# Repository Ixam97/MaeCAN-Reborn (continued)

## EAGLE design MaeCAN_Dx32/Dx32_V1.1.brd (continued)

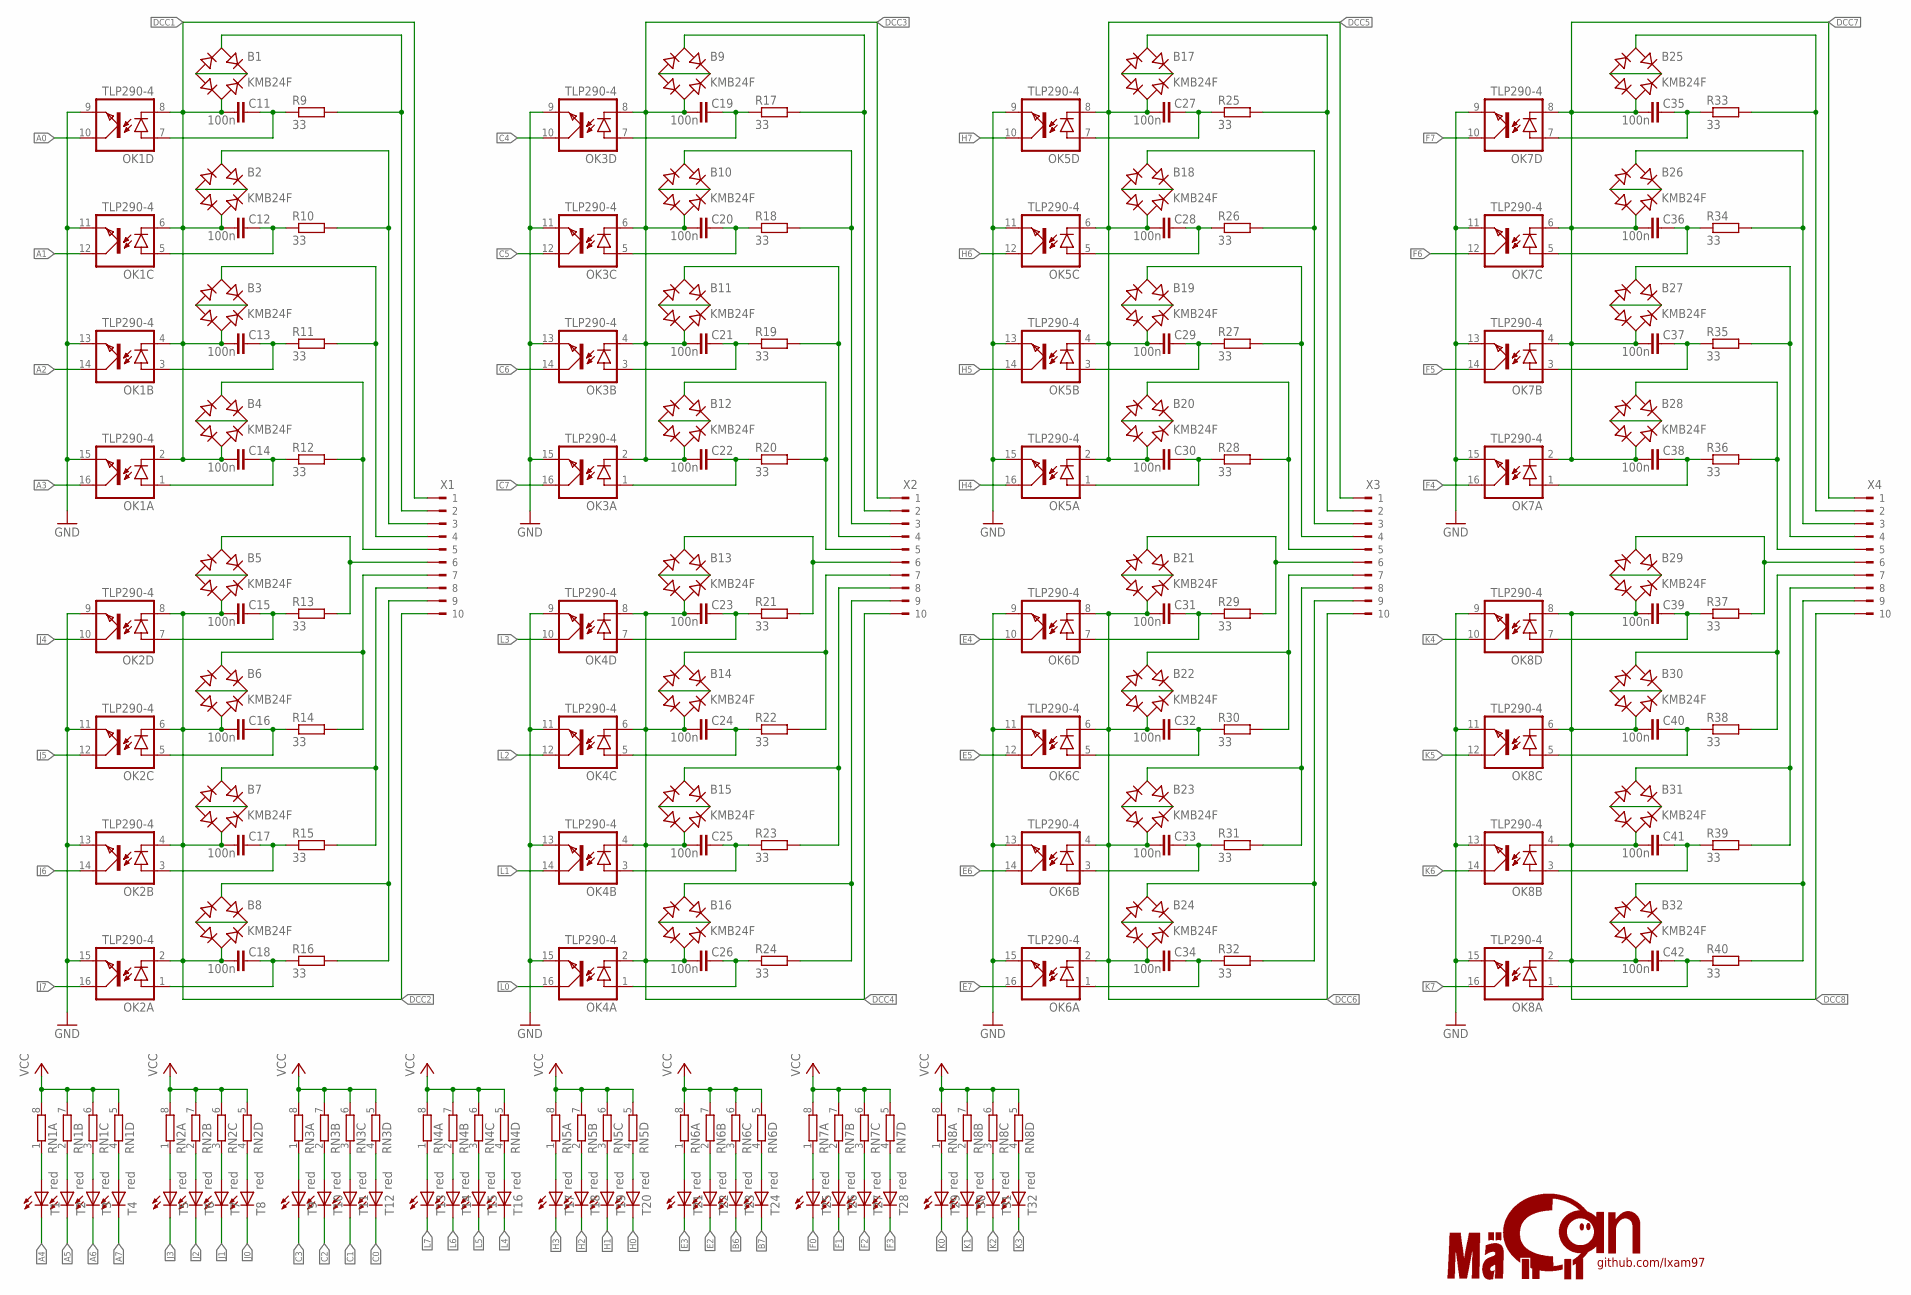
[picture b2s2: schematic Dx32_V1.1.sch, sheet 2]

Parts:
B1: KMB24F; MBS; JLCPCB-PART C113927
B2, B3, B4, B5, B6, B7, B8, B9, B10, B11, B12, B13, B14, B15, B16, B17, B18, B19, B20, B21, B22, B23, B24, B25, B26, B27, B28, B29, B30, B31, B32: KMB24F; MBS
C11, C12, C13, C14, C15, C16, C17, C18, C19, C20, C21, C22, C23, C24, C25, C26, C27, C28, C29, C30, C31, C32, C33, C34, C35, C36, C37, C38, C39, C40, C41, C42: 100n; C0402
OK1: TLP290-4; MINI-FLAT-16; JLCPC-PART C39031
OK2, OK3, OK4, OK5, OK6, OK7, OK8: TLP290-4; MINI-FLAT-16
R9, R10, R11, R12, R13, R14, R15, R16, R17, R18, R19, R20, R21, R22, R23, R24, R25, R26, R27, R28, R29, R30, R31, R32, R33, R34, R35, R36, R37, R38, R39, R40: 33; R0402
RN1, RN2, RN3, RN4, RN5, RN6, RN7, RN8: 4R-N0603-ARV; 0603-ARV
T1: red; CHIP-LED0805; JLCPCB-PART C84256
T2, T3, T4, T5, T6, T7, T8, T9, T10, T11, T12, T13, T14, T15, T16, T17, T18, T19, T20, T21, T22, T23, T24, T25, T26, T27, T28, T29, T30, T31, T32: red; CHIP-LED0805
X1, X2, X3, X4: 180-10

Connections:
A0: OK1.10 (COL); also elsewhere on the board
A1: OK1.12 (COL); also elsewhere on the board
A2: OK1.14 (COL); also elsewhere on the board
A3: OK1.16 (COL); also elsewhere on the board
A4: T1.C; also elsewhere on the board
A5: T2.C; also elsewhere on the board
A6: T3.C; also elsewhere on the board
A7: T4.C; also elsewhere on the board
B6: T23.C; also elsewhere on the board
B7: T24.C; also elsewhere on the board
C0: T12.C; also elsewhere on the board
C1: T11.C; also elsewhere on the board
C2: T10.C; also elsewhere on the board
C3: T9.C; also elsewhere on the board
C4: OK3.10 (COL); also elsewhere on the board
C5: OK3.12 (COL); also elsewhere on the board
C6: OK3.14 (COL); also elsewhere on the board
C7: OK3.16 (COL); also elsewhere on the board
DCC1: B1.AC2, B2.AC2, B3.AC2, B4.AC2, C11.2, C12.2, C13.2, C14.2, OK1.2 (C), OK1.4 (C), OK1.6 (C), OK1.8 (C), X1.1
DCC2: B5.AC2, B6.AC2, B7.AC2, B8.AC2, C15.2, C16.2, C17.2, C18.2, OK2.2 (C), OK2.4 (C), OK2.6 (C), OK2.8 (C), X1.10
DCC3: B9.AC2, B10.AC2, B11.AC2, B12.AC2, C19.2, C20.2, C21.2, C22.2, OK3.2 (C), OK3.4 (C), OK3.6 (C), OK3.8 (C), X2.1
DCC4: B13.AC2, B14.AC2, B15.AC2, B16.AC2, C23.2, C24.2, C25.2, C26.2, OK4.2 (C), OK4.4 (C), OK4.6 (C), OK4.8 (C), X2.10
DCC5: B17.AC2, B18.AC2, B19.AC2, B20.AC2, C27.2, C28.2, C29.2, C30.2, OK5.2 (C), OK5.4 (C), OK5.6 (C), OK5.8 (C), X3.1
DCC6: B21.AC2, B22.AC2, B23.AC2, B24.AC2, C31.2, C32.2, C33.2, C34.2, OK6.2 (C), OK6.4 (C), OK6.6 (C), OK6.8 (C), X3.10
DCC7: B25.AC2, B26.AC2, B27.AC2, B28.AC2, C35.2, C36.2, C37.2, C38.2, OK7.2 (C), OK7.4 (C), OK7.6 (C), OK7.8 (C), X4.1
DCC8: B29.AC2, B30.AC2, B31.AC2, B32.AC2, C39.2, C40.2, C41.2, C42.2, OK8.2 (C), OK8.4 (C), OK8.6 (C), OK8.8 (C), X4.10
E2: T22.C; also elsewhere on the board
E3: T21.C; also elsewhere on the board
E4: OK6.10 (COL); also elsewhere on the board
E5: OK6.12 (COL); also elsewhere on the board
E6: OK6.14 (COL); also elsewhere on the board
E7: OK6.16 (COL); also elsewhere on the board
F0: T25.C; also elsewhere on the board
F1: T26.C; also elsewhere on the board
F2: T27.C; also elsewhere on the board
F3: T28.C; also elsewhere on the board
F4: OK7.16 (COL); also elsewhere on the board
F5: OK7.14 (COL); also elsewhere on the board
F6: OK7.12 (COL); also elsewhere on the board
F7: OK7.10 (COL); also elsewhere on the board
GND: OK1.9 (EMIT), OK1.11 (EMIT), OK1.13 (EMIT), OK1.15 (EMIT), OK2.9 (EMIT), OK2.11 (EMIT), OK2.13 (EMIT), OK2.15 (EMIT), OK3.9 (EMIT), OK3.11 (EMIT), OK3.13 (EMIT), OK3.15 (EMIT), OK4.9 (EMIT), OK4.11 (EMIT), OK4.13 (EMIT), OK4.15 (EMIT), OK5.9 (EMIT), OK5.11 (EMIT), OK5.13 (EMIT), OK5.15 (EMIT), OK6.9 (EMIT), OK6.11 (EMIT), OK6.13 (EMIT), OK6.15 (EMIT), OK7.9 (EMIT), OK7.11 (EMIT), OK7.13 (EMIT), OK7.15 (EMIT), OK8.9 (EMIT), OK8.11 (EMIT), OK8.13 (EMIT), OK8.15 (EMIT); also elsewhere on the board
H0: T20.C; also elsewhere on the board
H1: T19.C; also elsewhere on the board
H2: T18.C; also elsewhere on the board
H3: T17.C; also elsewhere on the board
H4: OK5.16 (COL); also elsewhere on the board
H5: OK5.14 (COL); also elsewhere on the board
H6: OK5.12 (COL); also elsewhere on the board
H7: OK5.10 (COL); also elsewhere on the board
J0: T8.C; also elsewhere on the board
J1: T7.C; also elsewhere on the board
J2: T6.C; also elsewhere on the board
J3: T5.C; also elsewhere on the board
J4: OK2.10 (COL); also elsewhere on the board
J5: OK2.12 (COL); also elsewhere on the board
J6: OK2.14 (COL); also elsewhere on the board
J7: OK2.16 (COL); also elsewhere on the board
K0: T29.C; also elsewhere on the board
K1: T30.C; also elsewhere on the board
K2: T31.C; also elsewhere on the board
K3: T32.C; also elsewhere on the board
K4: OK8.10 (COL); also elsewhere on the board
K5: OK8.12 (COL); also elsewhere on the board
K6: OK8.14 (COL); also elsewhere on the board
K7: OK8.16 (COL); also elsewhere on the board
L0: OK4.16 (COL); also elsewhere on the board
L1: OK4.14 (COL); also elsewhere on the board
L2: OK4.12 (COL); also elsewhere on the board
L3: OK4.10 (COL); also elsewhere on the board
L4: T16.C; also elsewhere on the board
L5: T15.C; also elsewhere on the board
L6: T14.C; also elsewhere on the board
L7: T13.C; also elsewhere on the board
unnamed: B1.+, B1.-
unnamed: B1.AC1, R9.2, X1.2
unnamed: B5.+, B5.-
unnamed: C11.1, OK1.7 (A), R9.1
unnamed: B2.+, B2.-
unnamed: B2.AC1, R10.2, X1.3
unnamed: B3.+, B3.-
unnamed: C12.1, OK1.5 (A), R10.1
unnamed: B24.AC1, R32.2, X3.9
unnamed: C13.1, OK1.3 (A), R11.1
unnamed: B4.+, B4.-
unnamed: B4.AC1, R12.2, X1.5
unnamed: C14.1, OK1.1 (A), R12.1
unnamed: B5.AC1, R13.2, X1.6
unnamed: C15.1, OK2.7 (A), R13.1
unnamed: B6.+, B6.-
unnamed: B6.AC1, R14.2, X1.7
unnamed: C16.1, OK2.5 (A), R14.1
unnamed: B7.+, B7.-
unnamed: B7.AC1, R15.2, X1.8
unnamed: C17.1, OK2.3 (A), R15.1
unnamed: B8.+, B8.-
unnamed: B8.AC1, R16.2, X1.9
unnamed: C18.1, OK2.1 (A), R16.1
unnamed: RN1.1, T1.A
unnamed: RN1.2 (1), T2.A
unnamed: RN1.3 (1), T3.A
unnamed: RN1.4 (1), T4.A
unnamed: RN2.1, T5.A
unnamed: RN2.2 (1), T6.A
unnamed: RN2.3 (1), T7.A
unnamed: RN2.4 (1), T8.A
unnamed: B9.+, B9.-
unnamed: B9.AC1, R17.2, X2.2
unnamed: C19.1, OK3.7 (A), R17.1
unnamed: B10.+, B10.-
unnamed: B10.AC1, R18.2, X2.3
unnamed: C20.1, OK3.5 (A), R18.1
unnamed: B11.+, B11.-
unnamed: B11.AC1, R19.2, X2.4
unnamed: C21.1, OK3.3 (A), R19.1
unnamed: B12.+, B12.-
unnamed: B12.AC1, R20.2, X2.5
unnamed: C22.1, OK3.1 (A), R20.1
unnamed: B13.+, B13.-
unnamed: B13.AC1, R21.2, X2.6
unnamed: C23.1, OK4.7 (A), R21.1
unnamed: B14.+, B14.-
unnamed: B14.AC1, R22.2, X2.7
unnamed: C24.1, OK4.5 (A), R22.1
unnamed: B15.+, B15.-
unnamed: B15.AC1, R23.2, X2.8
unnamed: C25.1, OK4.3 (A), R23.1
unnamed: B16.+, B16.-
unnamed: B16.AC1, R24.2, X2.9
unnamed: C26.1, OK4.1 (A), R24.1
unnamed: B17.+, B17.-
unnamed: B17.AC1, R25.2, X3.2
unnamed: C27.1, OK5.7 (A), R25.1
unnamed: B18.+, B18.-
unnamed: B18.AC1, R26.2, X3.3
unnamed: C28.1, OK5.5 (A), R26.1
unnamed: B19.+, B19.-
unnamed: B19.AC1, R27.2, X3.4
unnamed: C29.1, OK5.3 (A), R27.1
unnamed: B20.+, B20.-
unnamed: B20.AC1, R28.2, X3.5
unnamed: C30.1, OK5.1 (A), R28.1
unnamed: B21.+, B21.-
unnamed: C31.1, OK6.7 (A), R29.1
unnamed: B22.+, B22.-
unnamed: B32.AC1, R40.2, X4.9
unnamed: C32.1, OK6.5 (A), R30.1
unnamed: B23.+, B23.-
unnamed: B23.AC1, R31.2, X3.8
unnamed: C33.1, OK6.3 (A), R31.1
unnamed: B24.+, B24.-
unnamed: B31.AC1, R39.2, X4.8
unnamed: C34.1, OK6.1 (A), R32.1
unnamed: B25.+, B25.-
unnamed: B25.AC1, R33.2, X4.2
unnamed: C35.1, OK7.7 (A), R33.1
unnamed: B26.+, B26.-
unnamed: B26.AC1, R34.2, X4.3
unnamed: C36.1, OK7.5 (A), R34.1
unnamed: B27.+, B27.-
unnamed: B27.AC1, R35.2, X4.4
unnamed: B3.AC1, R11.2, X1.4
unnamed: C37.1, OK7.3 (A), R35.1
unnamed: B28.+, B28.-
unnamed: B28.AC1, R36.2, X4.5
unnamed: C38.1, OK7.1 (A), R36.1
unnamed: B29.+, B29.-
unnamed: C39.1, OK8.7 (A), R37.1
unnamed: B30.+, B30.-
unnamed: C40.1, OK8.5 (A), R38.1
unnamed: B31.+, B31.-
unnamed: B30.AC1, R38.2, X4.7
unnamed: C41.1, OK8.3 (A), R39.1
unnamed: B32.+, B32.-
unnamed: C42.1, OK8.1 (A), R40.1
unnamed: RN3.1, T9.A
unnamed: RN3.2 (1), T10.A
unnamed: RN3.3 (1), T11.A
unnamed: RN3.4 (1), T12.A
unnamed: RN4.1, T13.A
unnamed: RN4.2 (1), T14.A
unnamed: RN4.3 (1), T15.A
unnamed: RN4.4 (1), T16.A
unnamed: B22.AC1, R30.2, X3.7
unnamed: RN5.1, T17.A
unnamed: RN5.2 (1), T18.A
unnamed: RN5.3 (1), T19.A
unnamed: RN5.4 (1), T20.A
unnamed: RN6.1, T21.A
unnamed: RN6.2 (1), T22.A
unnamed: RN6.3 (1), T23.A
unnamed: RN6.4 (1), T24.A
unnamed: RN7.1, T25.A
unnamed: RN7.2 (1), T26.A
unnamed: RN7.3 (1), T27.A
unnamed: RN7.4 (1), T28.A
unnamed: RN8.1, T29.A
unnamed: RN8.2 (1), T30.A
unnamed: RN8.3 (1), T31.A
unnamed: RN8.4 (1), T32.A
unnamed: B21.AC1, R29.2, X3.6
unnamed: B29.AC1, R37.2, X4.6
VCC: RN1.5 (2), RN1.6 (2), RN1.7 (2), RN1.8 (2), RN2.5 (2), RN2.6 (2), RN2.7 (2), RN2.8 (2), RN3.5 (2), RN3.6 (2), RN3.7 (2), RN3.8 (2), RN4.5 (2), RN4.6 (2), RN4.7 (2), RN4.8 (2), RN5.5 (2), RN5.6 (2), RN5.7 (2), RN5.8 (2), RN6.5 (2), RN6.6 (2), RN6.7 (2), RN6.8 (2), RN7.5 (2), RN7.6 (2), RN7.7 (2), RN7.8 (2), RN8.5 (2), RN8.6 (2), RN8.7 (2), RN8.8 (2); also elsewhere on the board

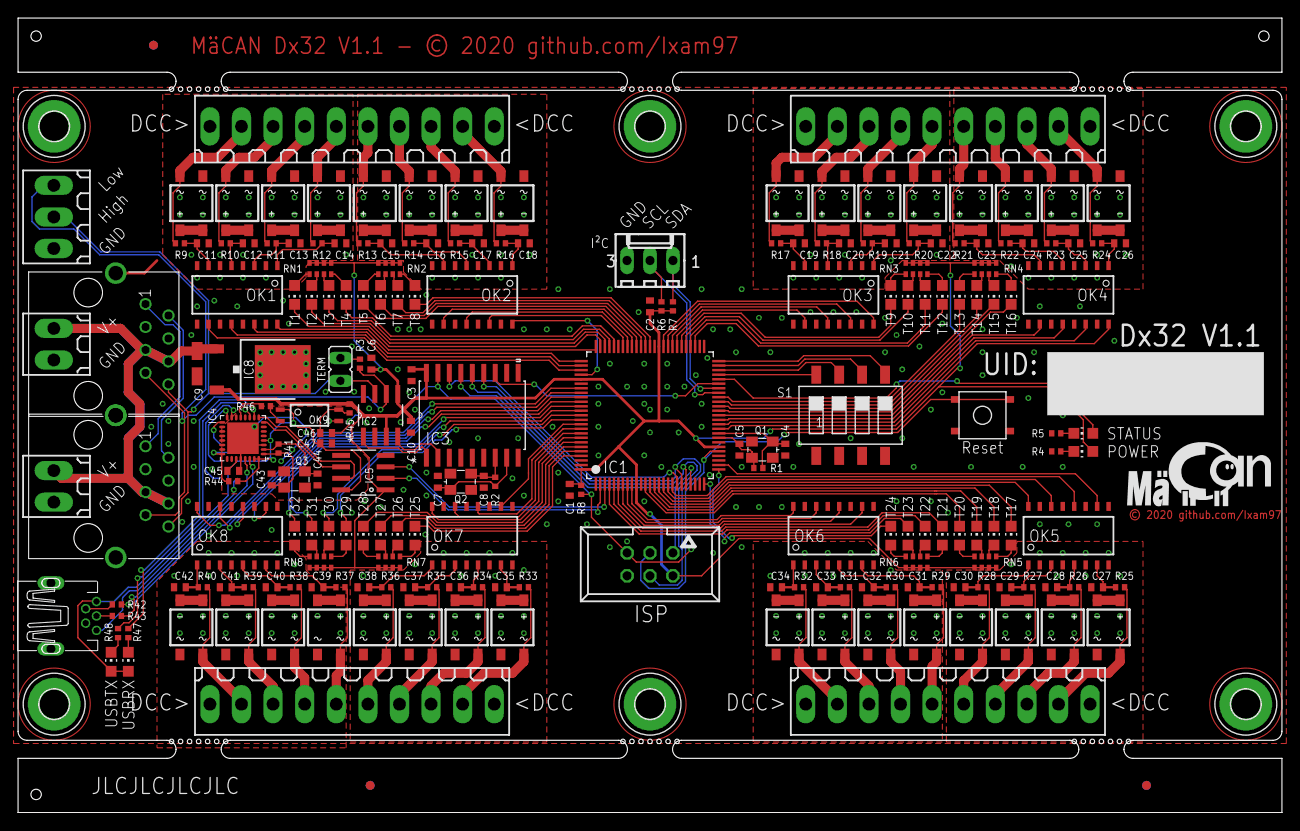
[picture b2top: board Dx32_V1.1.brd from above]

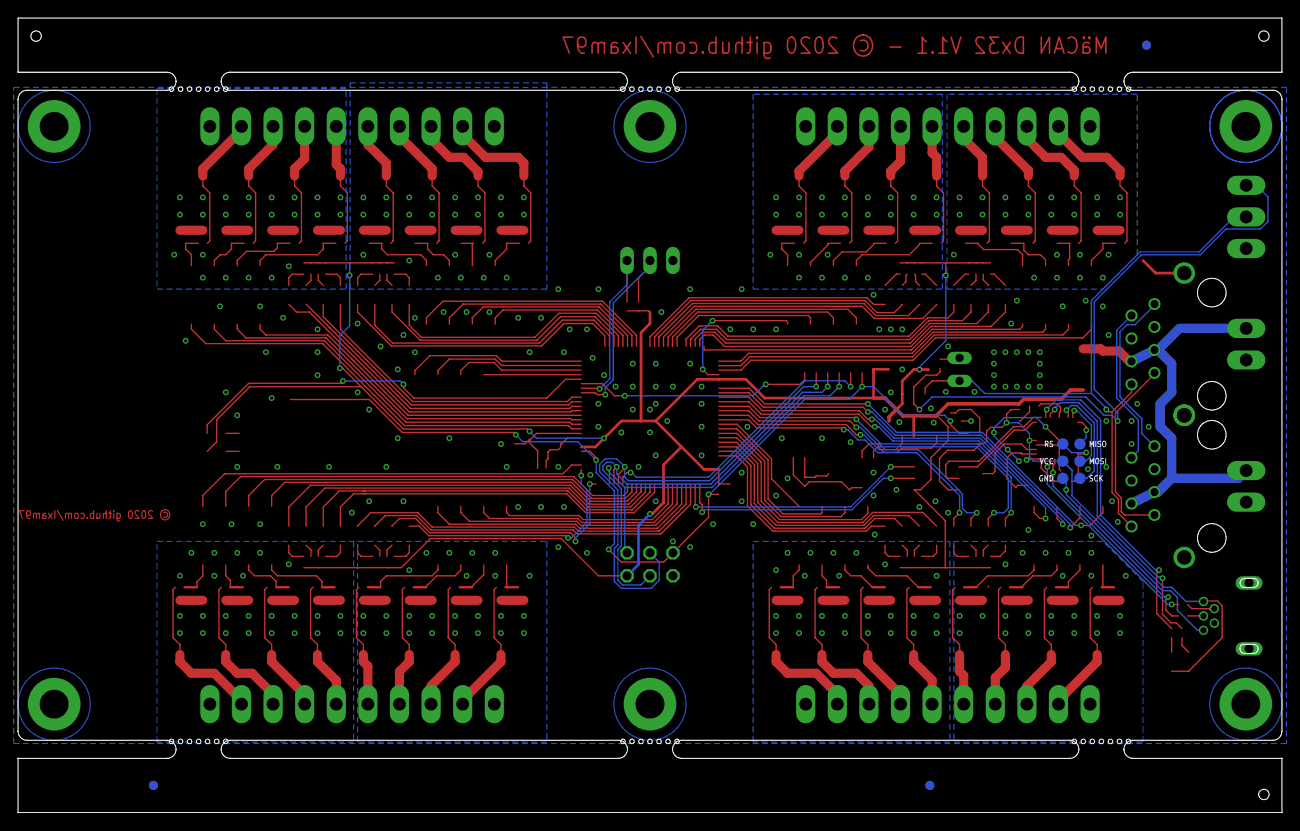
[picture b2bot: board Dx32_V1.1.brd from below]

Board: 2 copper layers, 140.0 x 88.0 mm, 229 parts (6 on the bottom side), 253 nets.

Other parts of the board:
U$2, U$3, U$5: JLCPCB_TOOLINGHOLE
U$6, U$7, U$8: FIDUCIAL
U$9, U$10, U$11, U$12, U$13, U$14: MOUSEBITESX7
U$17: LOGO_2

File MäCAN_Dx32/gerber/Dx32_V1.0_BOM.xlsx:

Qty | Designator | Footprint | Comment | LCSC Part #
8 | RN1, RN2, RN3, RN4, RN5, RN6, RN7, RN8 | 0603_x4 | 1k | C20197
1 | C9 | CASE-A_3216 | 10u | C7171
39 | C1, C2, C3, C6, C10, C11, C12, C13, C14, C15, C16, C17, C18, C19, C20, C21, C22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 | C0402 | 100n | C1525
5 | R6, R7, R8, R44, R45 | R0402 | 10k | C25744
1 | R3 | R0402 | 120 | C25079
3 | Q1, Q2, Q3 | 3.2X2.5_KX-7 | 16MHZ | C13738
3 | R1, R2, R41 | R0402 | 1M | C26083
4 | R4, R5, R47, R48 | R0402 | 1k | C11702
1 | C45 | C0402 | 1u | C52923
2 | R42, R43 | R0402 | 22 | C25092
6 | C4, C5, C7, C8, C43, C44 | C0402 | 22p | C1555
32 | R9, R10, R11, R12, R13, R14, R15, R16, R17, R18, R19, R20, R21, R22, R23, R24, 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 | R0402 | 33 | C25105
1 | R46 | R0402 | 330 | C25104
1 | IC5 | SOIC-8_3.9x4.9x1.27P | ADUM1201ARZ-RL7 | C9669
1 | IC4 | QFN-32_EP_5.0x5.0x0.5P | ATMEGA16U2 | C17317
1 | IC1 | QFP-100_14.0x14.0x0.5P | ATMEGA2560 | C22460
1 | RESET | SMD-SW-4 | TS-1187A-B-A-B | C318884
32 | B1, B2, B3, B4, B5, B6, B7, B8, B9, B10, B11, B12, B13, B14, B15, B16, B17, B18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 | MBF_3.8x4.7x2.5P | KMB24F | C113927
1 | IC8 | TO-252-2 | L78M05 | C58069
1 | IC3 | SOIC-18 | MCP2515-I/SO | C12368
1 | IC2 | SOIC-8 | TJA1050 | C6952
1 | S1 | SW-SMD-8_6.2x11.1x2.54P | DMR-04-V-T/R | C225009
1 | OK9 | SOP-4_2.7x4.4x1.27P | TLP290 | C73839
8 | OK1, OK2, OK3, OK4, OK5, OK6, OK7, OK8 | SOIC-16_4.4x10.3x1.27P | TLP290-4 | C39031
3 | STATUS, USBRX, USBTX | LED_0805 | yellow | C2296
33 | POWER, T1, T2, T3, T4, T5, T6, T7, T8, T9, T10, T11, T12, T13, T14, T15, T16, T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 | LED_0805 | red | C84256

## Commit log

2020-08-27 2020-08-27.2
2020-08-28 [2020-08-28.1]
    Unwichtige Datei gelöscht.
2020-12-22 [2020-12-22.1]
2020-12-26 [2020-12-26.1]
2020-12-26 [2020-12-26.2]
2021-01-05 [2020-01-05.1]
2021-01-05 [2021-01-05.1]
2021-01-24 [2021-01-24.1]
2021-01-25 [2021-01-25.1]
2021-01-27 [2021-01-27.1]
2021-03-12 [2021-03-12.1]
2021-03-13 [2021-03-13.1]
2021-03-13 [2021-03-13.2]
2021-09-14 [2021-09-14.1]
2022-03-06 [2022-03-06.1]
2022-03-07 [2022-03-07.1]
2022-03-26 [2022-03-26.1]
2022-03-26 [2022-03-26.2]
